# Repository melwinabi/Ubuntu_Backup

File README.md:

# Ubuntu 24.04 Migration Backup

This repository contains the backup of personal files, projects, and system configurations prior to Windows installation.

## Directory Structure
- `srm/`: Pinned SRM project & study materials
- `Documents/`: All active code repositories, electronics designs, PlatformIO, KiCad, embedded projects, and work documents
- `Downloads/`: Important documents, PDFs, datasheets, resumes, and project downloads
- `Pictures/`: Personal photos and images
- `Music/` & `Videos/`: Media directories
- `system_info/`: Complete list of installed APT packages, Snap packages, and system specs for reference on Windows.
- `Antigravity_Chats/`: Complete archive of all Google Antigravity R&D chat histories, implementation plans, architecture artifacts, and conversation database.

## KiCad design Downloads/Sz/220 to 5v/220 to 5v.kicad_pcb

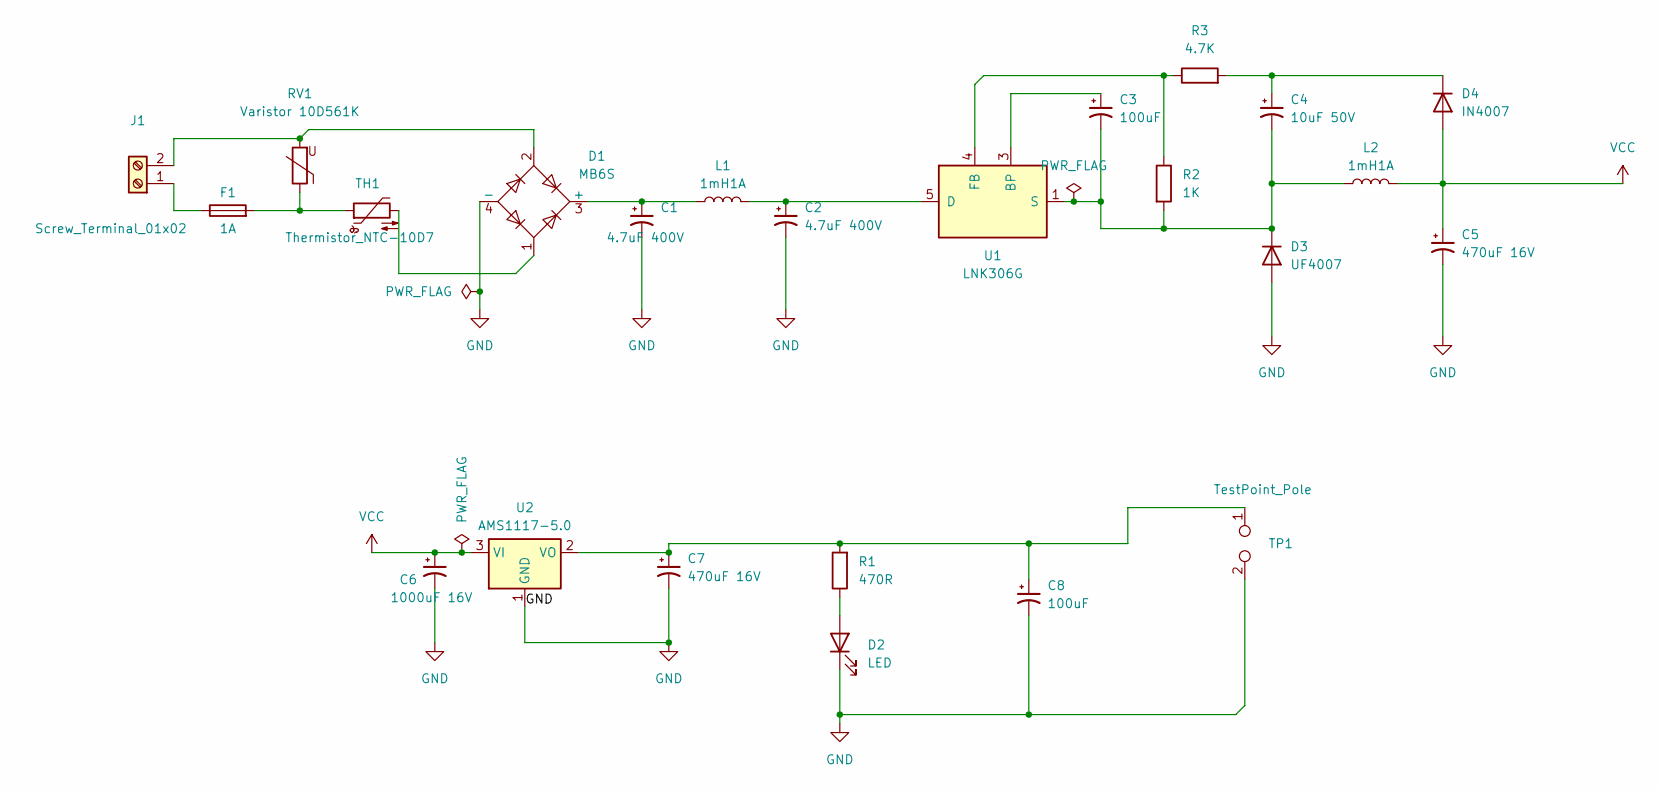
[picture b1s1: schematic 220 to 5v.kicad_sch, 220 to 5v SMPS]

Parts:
C1, C2: 4.7uF 400V; CP_Elec_10x10
C3, C8: 100uF; D_2114_3652Metric_Pad1.85x3.75mm_HandSolder
C4: 10uF 50V; CP_Elec_5x5.3
C5, C7: 470uF 16V; CP_Elec_6.3x9.9
C6: 1000uF 16V; CP_Elec_8x10
D1: MB6S; TO-269AA
D2: LED; LED_D5.0mm_Clear
D3: UF4007; D_2114_3652Metric_Pad1.85x3.75mm_HandSolder
D4: IN4007; D_2114_3652Metric_Pad1.85x3.75mm_HandSolder
F1: 1A; Fuse_0805_2012Metric
J1: Screw_Terminal_01x02; TerminalBlock_Phoenix_MKDS-1,5-2_1x02_P5.00mm_Horizontal
L1, L2: 1mH1A; L_10.4x10.4_H4.8
R1: 470R; R_0805_2012Metric_Pad1.20x1.40mm_HandSolder
R2: 1K; R_0805_2012Metric_Pad1.20x1.40mm_HandSolder
R3: 4.7K; R_0805_2012Metric_Pad1.20x1.40mm_HandSolder
RV1: Varistor 10D561K; RV_Disc_D9mm_W6.1mm_P5mm
TH1: Thermistor_NTC-10D7; R_Axial_DIN0309_L9.0mm_D3.2mm_P2.54mm_Vertical
TP1: TestPoint_Pole; PinHeader_1x02_P1.27mm_Vertical
U1: LNK306G; PowerIntegrations_SMD-8B
U2: AMS1117-5.0; SOT-223-3_TabPin2

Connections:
GND: C1.2, C2.2, C5.2, C6.2, C7.2, C8.2, D1.4 (-), D2.1 (K), D3.2 (A), TP1.2, U2.1 (GND)
unnamed: C1.1, D1.3 (+), L1.1
unnamed: D1.1, TH1.2
unnamed: D2.2 (A), R1.1
unnamed: C3.2, C4.2, D3.1 (K), L2.1, R2.2, U1.1 (S), U1.2 (S), U1.7 (S), U1.8 (S)
unnamed: C4.1, D4.1 (K), R3.2
unnamed: F1.2, RV1.1, TH1.1
unnamed: F1.1, J1.1
unnamed: D1.2, J1.2, RV1.2
unnamed: C3.1, U1.3 (BP)
unnamed: C2.1, L1.2, U1.5 (D)
unnamed: R2.1, R3.1, U1.4 (FB)
unnamed: C7.1, C8.1, R1.2, TP1.1, U2.2 (VO)
VCC: C5.1, C6.1, D4.2 (A), L2.2, U2.3 (VI)

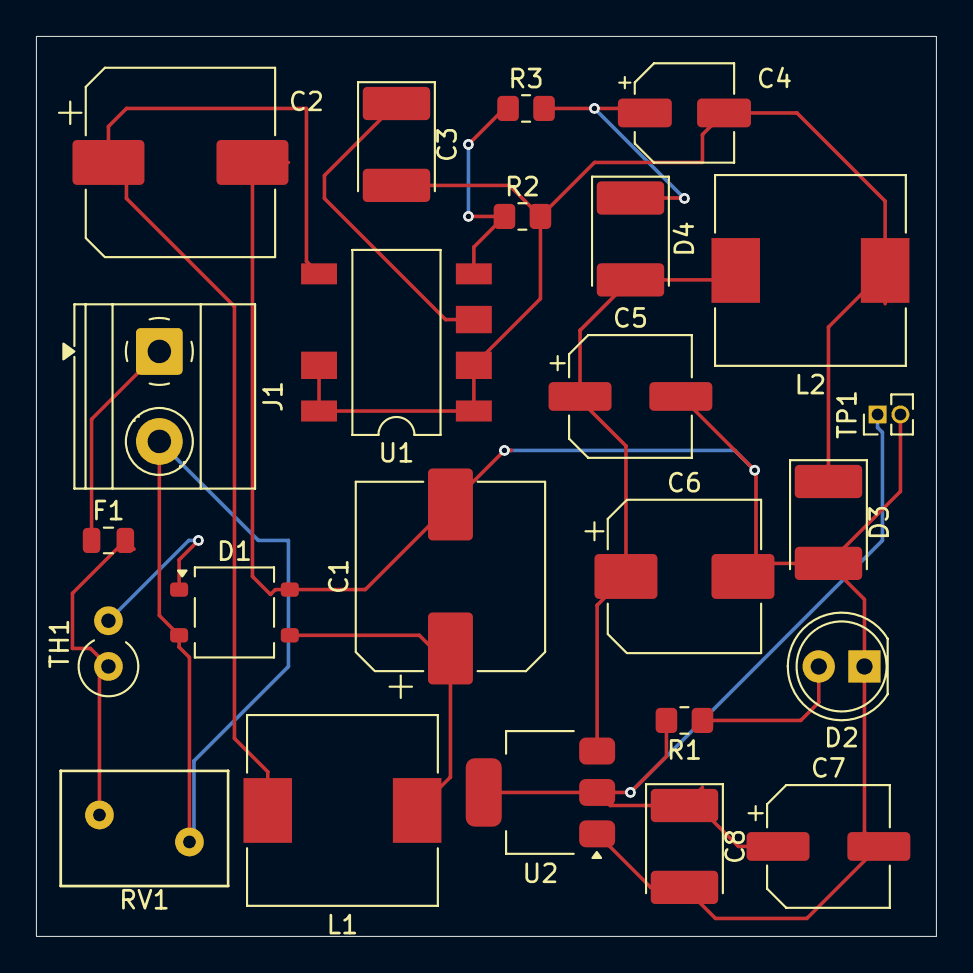
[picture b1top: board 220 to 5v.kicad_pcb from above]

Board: 2 copper layers, 50.0 x 50.0 mm, 24 parts (0 on the bottom side), 14 nets.
